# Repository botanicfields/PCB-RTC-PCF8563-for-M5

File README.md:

## PCB-RTC-PCF8563-for-M5
a PCB of PCF8563-RTC with Grove-I2C for M5Stack and M5Atom synchronized with NTP

# M5 用リアルタイムクロック (RTC) 基板

　M5 シリーズ用に作成した RTC 基板です。水晶振動子 により高精度に時刻を刻みます。バッテリ・バックアップにより本体が電源オフの状態でも時刻を維持します。

- M5 仕様の Grove コネクタ

    　M5 製品の Grove コネクタ仕様（電源 5V, 信号レベル 3.3V）に合致します。Grove コネクタが 2 個あり、I2C デバイスの数珠つなぎができます。

- M5 製品と同仕様の RTC

    　M5Core2, M5StickC/C Plus, M5CoreInk, M5Paper, M5Camera/F/X に内蔵されている BM8563 と互換の RTC(PCF8563) を搭載し、M5 用の多くのソフトウェアを利用できます。

- INT, CLKO 信号出力

    　PCF8563(BM8563) の INT 信号、CLKO 信号を、基板上のピンソケットから取り出せます。これらの信号は 3.3V に 10kΩ でプルアップしています。基板上の LED（INT: 赤、CLKO： 緑）で信号オンを確認できます。

- 時刻の精度を改善

    　基板上にトリマコンデンサを搭載し、時刻の精度を改善できます。出荷時には、以下の機器を用いて室温（15 - 25 ℃程度のどこか）にて調整済です。（※固定コンデンサ C4, トリマコンデンサ C5 はどちらか一方を実装します。トリマコンデンサを実装している場合、C4 には部品がありません。）

>> 1. 周波数カウンタ (1) を GPS 受信機 (2) の 1PPS 信号で校正
>>>> (1) 秋月電子通商「８桁周波数カウンターキット」 [AE-FCOUNT3](
https://akizukidenshi.com/catalog/g/gK-13432/)
>>>>
>>>> (2) 秋月電子通商「ＧＰＳ受信機キット～」 [AE-GYSFDMAXB](
https://akizukidenshi.com/catalog/g/gK-09991/)
>> 2. RTC 基板の CLKO から 1Hz 信号を取り出し、1PPS の代わりに入力
>> 3. 周波数カウンタの表示が所定の値に近づく様、RTC 基板上のトリマを調整

# ソフトウェア
　RTC の使用にあたっては、一般に入手可能なライブラリを利用することができます。

　他の I2C デバイスとの共存や、NTP との相互補完を想定したサンプルプログラムを作成し、BF-027 フォルダに置きました。詳細な説明は Qiita（参考を参照）にあります。これらのプログラムは M5Stack 社の [RTC ユニット](https://docs.m5stack.com/en/unit/rtc)でも使用できます。

1. BF_Pcf8563.h, BF_Pcf8563.cpp

    RTC PCF8563(BM8563) にアクセスし、時刻、アラーム、タイマー、クロック出力などの機能を使用するためのドライバです。

2. BF_Pcf8563Test.h, BF_Pcf8563Test.cpp

    上記 BF_Pcf8563.cpp の機能をテストするプログラムです。

3. BF_RtcxNtp.h, BF_RtcxNtp.cpp

    RTC と NTP を相互補完的に使用するためのプログラムです。

4. BF-027.ino

    上記プログラムの使用例です。  
- M5Stack または M5Atom で動作します。冒頭の #define で使用する方を残してコメントアウトしてください。  
- M5Atomでは RTC の接続先を GROVE コネクタか、またはピンソケットのどちらかを選べます。setup() の rtcx.Begin(Wire1) または rtcx.Begin(Wire) の使用するほうを残してコメントアウトしてください。

# 参考

(1) Qiita [「M5Atom, M5Stack Core 用の I2C リアルタイムクロック基板を作って動かす」](https://qiita.com/BotanicFields/items/dc35e12423be8f6e9b4e)

(2) Qiita [「ESP32 において NTP の時刻同期を捕まえて RTC を更新する」](https://qiita.com/BotanicFields/items/f1e28af5a63e4ccf7023)

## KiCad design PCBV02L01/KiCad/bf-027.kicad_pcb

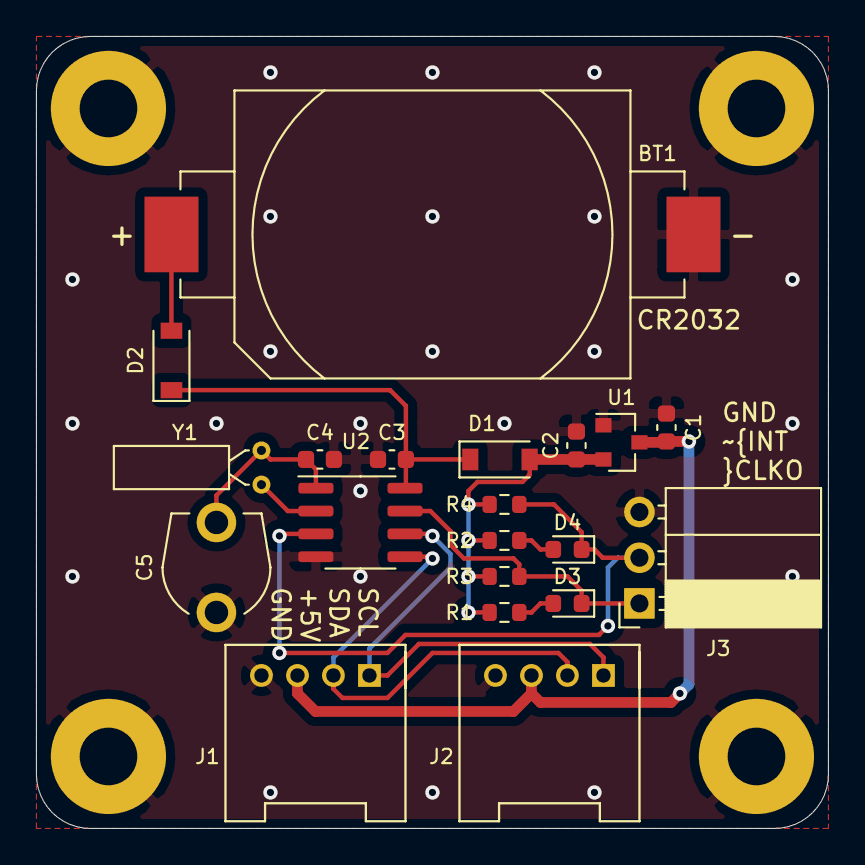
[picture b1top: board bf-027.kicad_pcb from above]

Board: 2 copper layers, 44.0 x 44.0 mm, 20 parts (0 on the bottom side), 13 nets.

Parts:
BT1: CR2032; BF@QJ-BS-6
C1, C2: 1u; C_0603_1608Metric
C3: 100n; C_0603_1608Metric
C4: 15p; C_0603_1608Metric
C5: 30p; BF@TZ03-F
D1, D2: 1N4148; D_SOD-123
D3: GREEN; LED_0603_1608Metric
D4: RED; LED_0603_1608Metric
J1, J2: I2C; HW4-2.0-90D
J3: OUT; BF@PinSocket_1x03_P2.54mm_Horizontal
R1, R2: 2.2k; R_0603_1608Metric
R3, R4: 10k; R_0603_1608Metric
U1: XC6206P332MR; SOT-23
U2: PCF8563T; SOIC-8_3.9x4.9mm_P1.27mm
Y1: 32768Hz; BF@Crystal_DS26_D2.0mm_L6.0mm_Horizontal

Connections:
/CLKO: D3.1, J3.1, R3.2, U2.7
/INT: D4.1, J3.2, R4.2, U2.3
/SCL: J1.1, J2.1, U2.6
/SDA: J1.2, J2.2, U2.5
GND: BT1.2, C1.2, C2.2, C3.2, C4.2, C5.2, J1.4, J2.4, J3.3, U1.1, U2.4
unnamed: BT1.1, D2.2
unnamed: C1.1, J1.3, J2.3, U1.3
unnamed: C2.1, D1.2, R1.1, R2.1, R3.1, R4.1, U1.2
unnamed: C3.1, D1.1, D2.1, U2.8
unnamed: C4.1, C5.1, U2.1, Y1.1
unnamed: D3.2, R1.2
unnamed: D4.2, R2.2
unnamed: U2.2, Y1.2

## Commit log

2021-05-11 Create LICENSE
2021-05-13 new
    new release
2021-05-14 Update README.md
    add image
2021-05-14 BF_RtcxNtp
    correct mistake of int to void
2021-05-14 trim trailing whitespaces
2021-05-15 Update BF-027.ino
    selection of M5Stack/M5Atom
2021-05-16 image with M5Stack Core Basic
2021-05-16 BOM, POS for JLCPCB
    update
2021-05-17 Update BF-027.ino
    using #indef - #endif instead of commenting out
2021-05-17 Update BF-027.ino
    reduced #ifdef - #endif
2021-05-24 update BF-027
    Improve of including header files
2021-05-24 Update BF_RtcxNtp.cpp
    set a tentative time if the RTC is invalid
2021-06-01 doc replaced
    button battery --> (coin) battery
2021-09-19 Arduino-ESP32 2.0.0
    <time.h>
    panic of WifiManager
2021-10-07 Update BF_Pcf8563.cpp
    fix bug of tm_mon in ReadTime
2021-11-07 update library
    INT demo removed from trimmer adjust
2021-11-13 M5 Board Manager 2.0.0
    I2C process to update RTCx by SNTP callback, etc.
2021-11-13 Update BF_RtcxNtp.cpp
    activate: sntp_get_sync_interval
2022-02-11 Update BF-027.ino
    use unsigned int for millisec
2022-09-09 example updated
    example codes are updated
2022-09-09 Update BF_Pcf8563Test.cpp
    Refined: serial.printf format of TimeSpec

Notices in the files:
PCBV02L01/KiCad/bf-027.kicad_pcb:
Copyright 2021 BotanicFields, Inc.
